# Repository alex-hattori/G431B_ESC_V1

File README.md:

# G431B_ESC_V1

Yet another port of the Mini Cheetah motor controller firmware; this time to ST's G431B-ESC dev board. https://www.st.com/en/evaluation-tools/b-g431b-esc1.html

Firmware architecture based on: https://github.com/bgkatz/motorcontrol

Some hardware calculations and hardware specific implementation details from: https://github.com/pat92fr/BrushlessServoController and https://github.com/simplefoc/Arduino-FOC 

____________________________________________________________________________________________________________________________________________________________________________________
Main branch uses an AS50XX (in my case, an AS5048A) external encoder on a custom breakout (gerbers, stp, and Eagle files in 'Hardware' folder). 

Communicates over 3 wire SPI (firmware bitbangs due to lack of broken out SPI peripheral pins on dev board). 

To use the breakout, do not populate the 5V->3V3 shorting jumper. Populate the MOSI pullup jumper (MOSI needs to be pulled high when not used).

To use SPI, the 3 resistors boxed in the wiring image need to be replaced with 0ohm 0402 resistors (or bridged with solder). 

____________________________________________________________________________________________________________________________________________________________________________________
Various branches have varying support of I2C and PWM encoder implementations. Use of I2C and PWM encoders do not require modification of the dev board. 

 ____________________________________________________________________________________________________________________________________________________________________________________

**Done:**

Serial

Flash

Encoder (3 Wire SPI, I2C, PWM)

PWM

Current Sense

State Machine

FOC (10khz)

CAN

Mosfet temperature sense

**Next Steps**

Increase loop frequency

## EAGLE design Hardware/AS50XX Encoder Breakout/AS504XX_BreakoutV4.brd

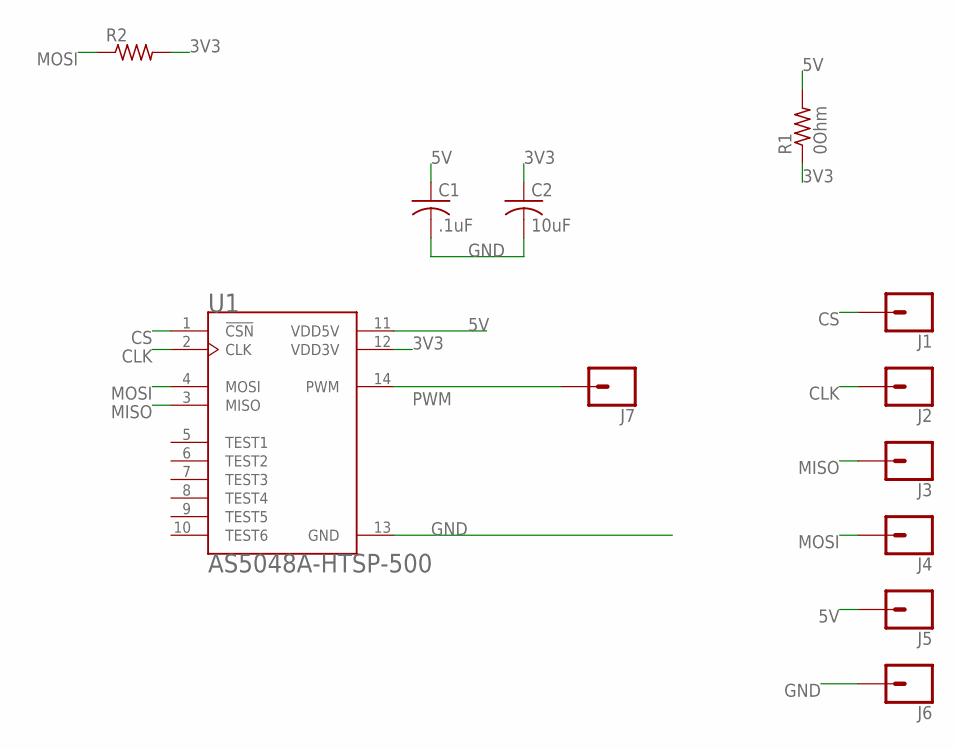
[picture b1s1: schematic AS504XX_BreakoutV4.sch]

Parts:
C1: .1uF; C0402
C2: 10uF; C0402
J1, J2, J3, J4, J5, J6, J7: CONN_01; 1X01
R1: 0Ohm; R0402
R2: R-US_R0603; R0603
U1: AS5048A-HTSP-500; SOP65P640X120-14N

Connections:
3V3: C2.1, R1.1, R2.2, U1.12 (VDD3V)
5V: C1.1, J5.1, R1.2, U1.11 (VDD5V)
CLK: J2.1, U1.2 (CLK)
CS: J1.1, U1.1 (!CSN)
GND: C1.2, C2.2, J6.1, U1.13 (GND)
MISO: J3.1, U1.3 (MISO)
MOSI: J4.1, R2.1, U1.4 (MOSI)
PWM: J7.1, U1.14 (PWM)

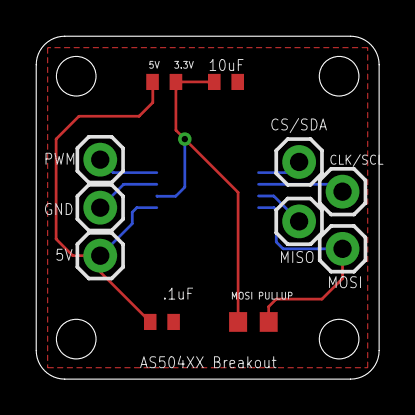
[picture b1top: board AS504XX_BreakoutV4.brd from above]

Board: 2 copper layers, 19.1 x 19.1 mm, 12 parts (1 on the bottom side), 8 nets.

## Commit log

2023-02-08 Working float flash memory
2023-02-08 Added Int Flash Implementation
2023-02-08 Cleaned Up Flash Implementation
2023-02-08 Update README.md
    Update README.md
    Update README.md
    Update README.md
    Update README.md
2023-02-10 Initial I2C encoder implementation
2023-02-11 Tested I2C, PWM, and Timer Loop
2023-02-11 Implemented ADC, FOC, FSM, Calibration, OpAmp
    No CAN yet
2023-02-13 Backup Before I2C Change
2023-02-13 Test I2C DMA
2023-02-14 Working FOC at 15khz loop
2023-02-14 Revert "Test I2C DMA"
    This reverts commit 3ae0bb29d64e625b6d0a7df0721624c1938f3736.
2023-02-16 Working CAN
2023-02-16 Minor Code Cleanup
2023-02-16 Added FET temp sensing
2023-02-17 I2C DMA. Actual 15khz control
2023-02-22 Investigating high speed commutation bug
2023-02-22 Ready to test
2023-02-22 Once per rotation clicking was due to linearization bug
    Need to solve still
2023-02-23 Bitbang AS5048A Working
    Removed and shorted R74, R75, R77
2023-03-04 Init PWM 5048A functionality
2023-03-30 Fixed encoder hardware
    Needed to tie floating MOSI on AS5048A to 3v3. Works!
2023-03-30 Revert "Once per rotation clicking was due to linearization bug"
    This reverts commit 3349f0c008c3ecf552f10526e2486182c5b518d6.
2023-03-30 Revert "Investigating high speed commutation bug"
    This reverts commit 928936f7a15349bd8bf3afd12124082010479709.
2023-03-30 Confirmed 10khz loop
    Can probably go faster
2023-05-12 Added Hardware Implementation Details
2023-10-06 Added STLink Flash Details
2024-04-13 Corrected encoder linearization math

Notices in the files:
parts and their libraries:
SparkFun-Connectors: Licensing: Creative Commons ShareAlike 4.0 International - https://creativecommons.org/licenses/by-sa/4.0
